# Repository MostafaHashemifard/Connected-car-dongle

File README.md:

# Connected-car-dongle
A device that is used to make cars connected to the cloud

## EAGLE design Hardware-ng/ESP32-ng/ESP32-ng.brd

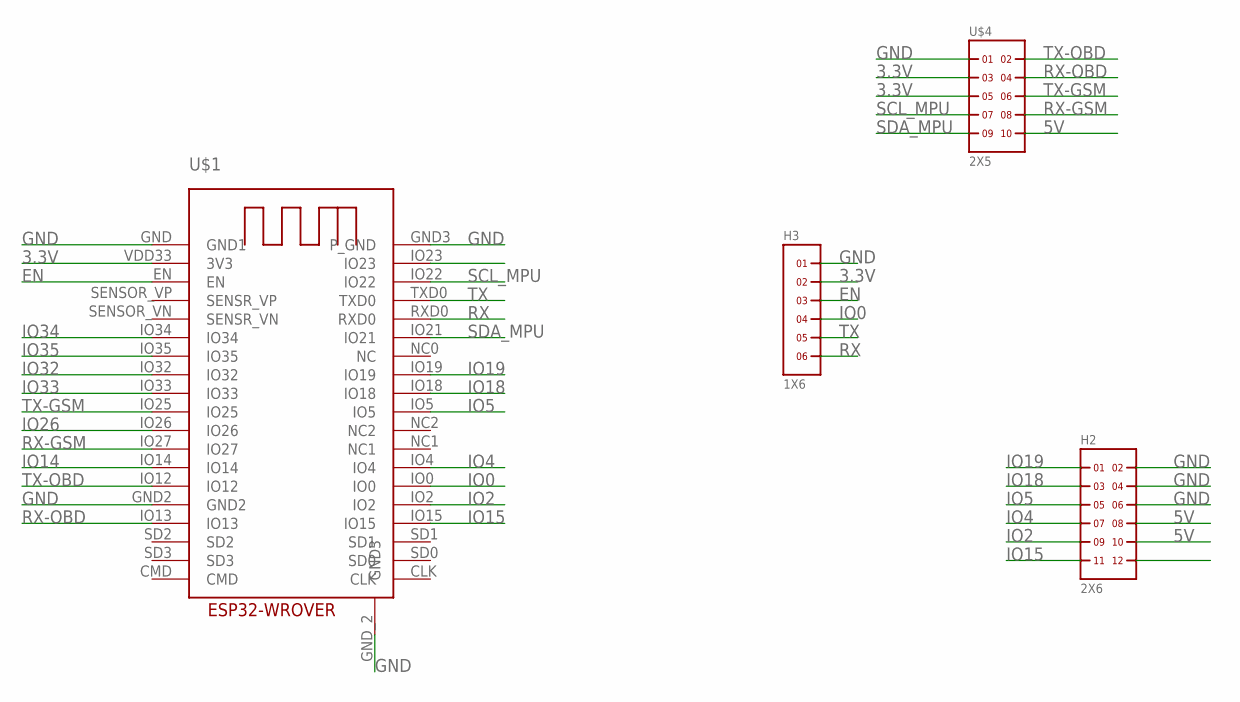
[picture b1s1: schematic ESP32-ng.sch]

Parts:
H2: 2X6
H3: 1X6
U$1: ESP32-WROVER
U$4: 2X5

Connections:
3.3V: H3.2, U$1.VDD33 (3V3), U$4.3, U$4.5
5V: H2.8, H2.10, U$4.10
EN: H3.3, U$1.EN
GND: H2.2, H2.4, H2.6, H3.1, U$1.GND (GND1), U$1.GND2, U$1.GND3 (P_GND), U$1.GND_2 (GND3), U$4.1
IO0: H3.4, U$1.IO0
IO2: H2.9, U$1.IO2
IO4: H2.7, U$1.IO4
IO5: H2.5, U$1.IO5
IO14: U$1.IO14
IO15: H2.11, U$1.IO15
IO18: H2.3, U$1.IO18
IO19: H2.1, U$1.IO19
IO26: U$1.IO26
IO32: U$1.IO32
IO33: U$1.IO33
IO34: U$1.IO34
IO35: U$1.IO35
RX: H3.6, U$1.RXD0
RX-GSM: U$1.IO27, U$4.8
RX-OBD: U$1.IO13, U$4.4
SCL_MPU: U$1.IO22, U$4.7
SDA_MPU: U$1.IO21, U$4.9
TX: H3.5, U$1.TXD0
TX-GSM: U$1.IO25, U$4.6
TX-OBD: U$1.IO12, U$4.2

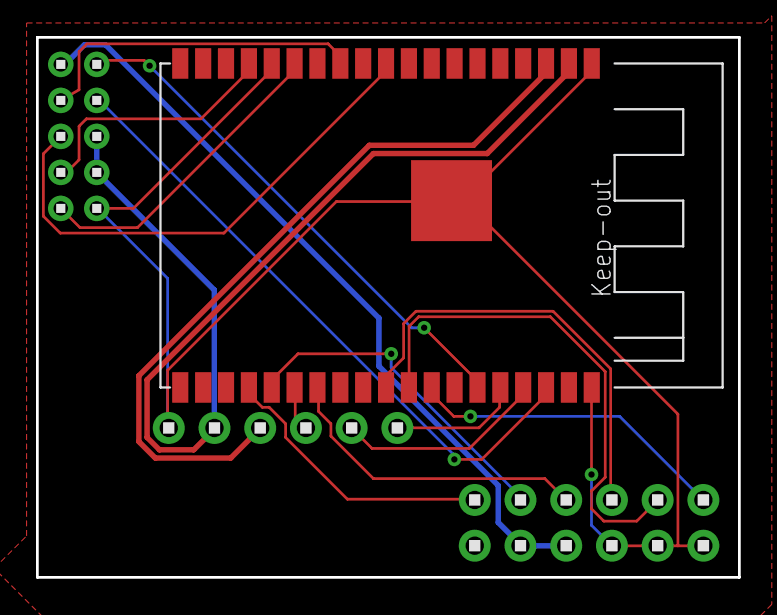
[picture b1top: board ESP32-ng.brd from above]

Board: 2 copper layers, 39.0 x 30.0 mm, 4 parts (0 on the bottom side), 19 nets.

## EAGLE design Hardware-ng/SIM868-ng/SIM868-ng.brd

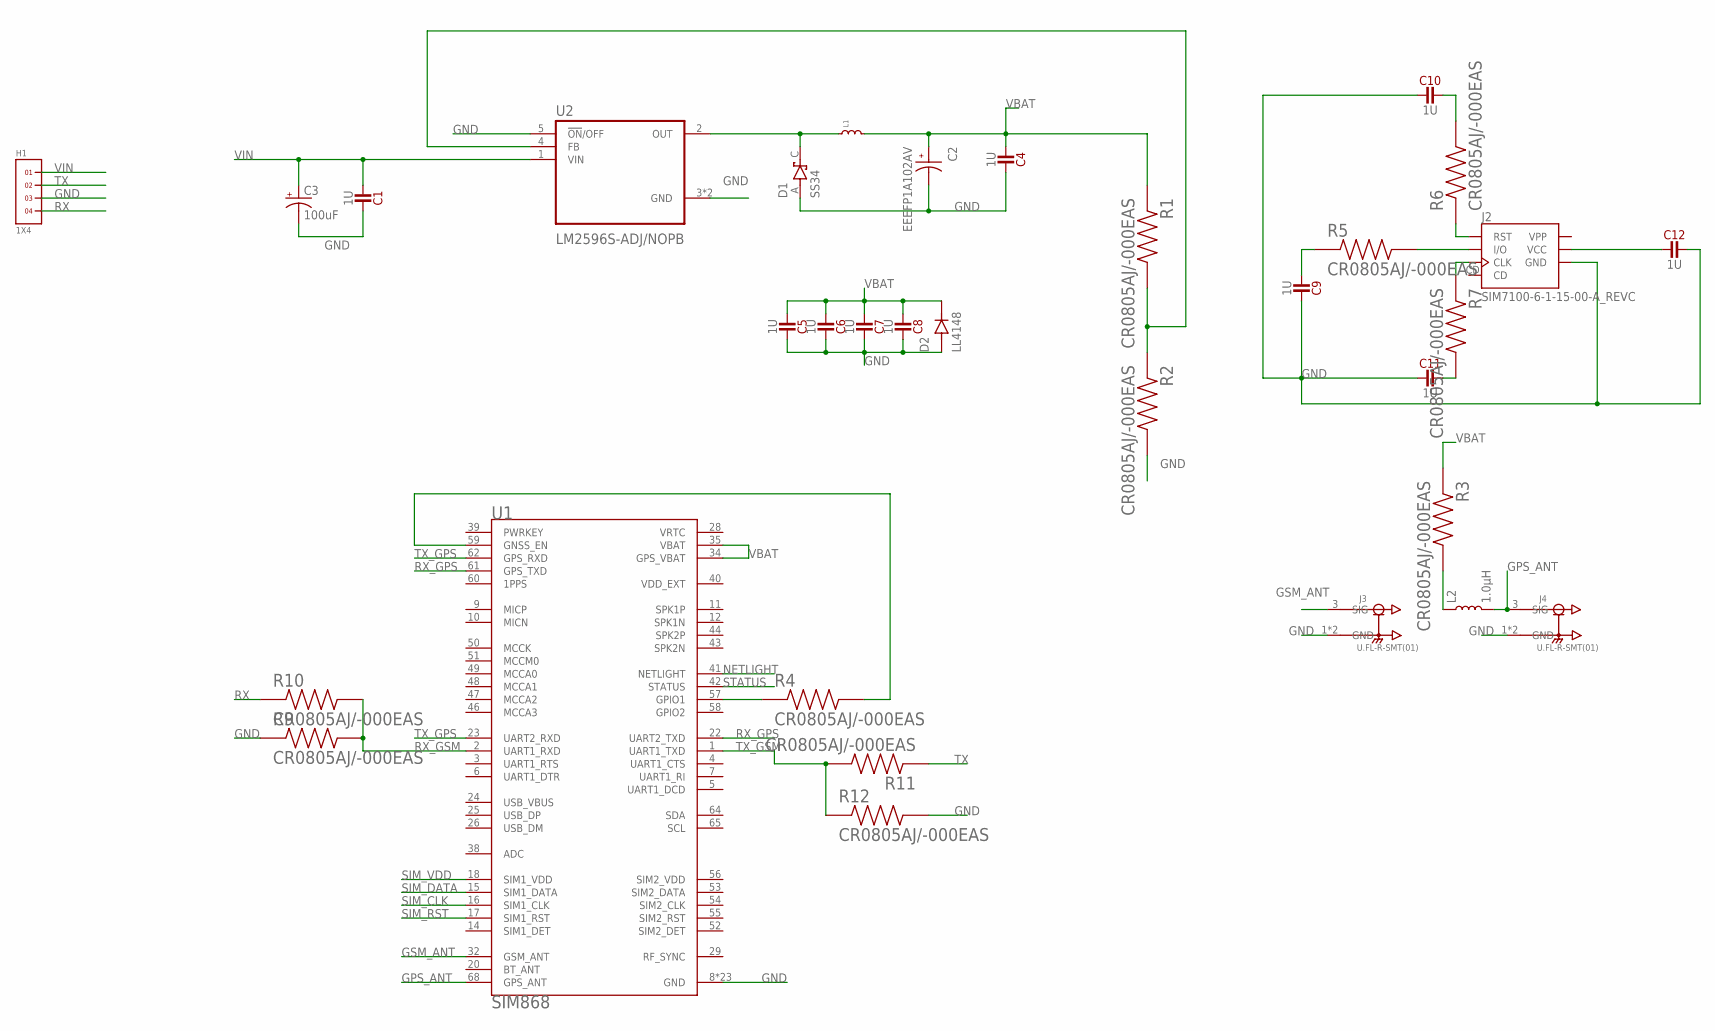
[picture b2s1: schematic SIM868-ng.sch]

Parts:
C1, C4, C5, C6, C7, C8, C9, C10, C11, C12: 1U; C-0805
C2: EEEFP1A102AV; CAP_EEEFP1A102AV
C3: 100uF; EIA3528
D1: SS34; DIOM7959X265N
D2: LL4148; DIO_LL4148
H1: 1X4
J2: SIM7100-6-1-15-00-A_REVC; GCT_SIM7100-6-1-15-00-A_REVC
J3, J4: U.FL-R-SMT(01); HRS_U.FL-R-SMT(01)
L1: INDUCTOR.XAL1010; XAL1010
L2: 1.0μH; 0805-WIDE
R1, R2, R3, R4, R5, R6, R7, R9, R10, R11, R12: CR0805AJ/-000EAS; RESC2012X60N
U1: SIM868; XCVR_SIM868
U2: LM2596S-ADJ/NOPB; VREG_LM2596S-ADJ/NOPB

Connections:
GND: C1.2, C2.2, C3.C (-), C4.2, C5.2, C6.2, C7.2, C8.2, C9.2, C10.1, C11.1, C12.2, D1.A, D2.A, H1.3, J2.C5 (GND), J3.1 (GND), J3.2 (GND), J4.1 (GND), J4.2 (GND), R2.2, R9.1, R12.2, U1.8 (GND), U1.13 (GND), U1.19 (GND), U1.21 (GND), U1.27 (GND), U1.30 (GND), U1.31 (GND), U1.33 (GND), U1.36 (GND), U1.37 (GND), U1.45 (GND), U1.63 (GND), U1.66 (GND), U1.67 (GND), U1.69 (GND), U1.70 (GND), U1.71 (GND), U1.72 (GND), U1.73 (GND), U1.74 (GND), U1.75 (GND), U1.76 (GND), U1.77 (GND), U2.3 (GND), U2.5 (!ON!/OFF), U2.6 (GND)
GPS_ANT: J4.3 (SIG), L2.2, U1.68 (GPS_ANT)
GSM_ANT: J3.3 (SIG), U1.32 (GSM_ANT)
unnamed: D1.C (K), L1.P$1 (1), U2.2 (OUT)
unnamed: R4.1, U1.57 (GPIO1)
unnamed: R1.2, R2.1, U2.4 (FB)
unnamed: L2.1, R3.2
unnamed: R4.2, U1.59 (GNSS_EN)
unnamed: J2.C7 (I/O), R5.2
unnamed: C9.1, R5.1
unnamed: J2.C2 (RST), R6.1
unnamed: C10.2, R6.2
unnamed: C11.2, R7.2
unnamed: J2.C3 (CLK), R7.1
unnamed: C12.1, J2.C1 (VCC)
NETLIGHT: U1.41 (NETLIGHT)
RX: H1.4, R10.1
RX_GPS: U1.22 (UART2_TXD), U1.61 (GPS_TXD)
RX_GSM: R9.2, R10.2, U1.2 (UART1_RXD)
SIM_CLK: U1.16 (SIM1_CLK)
SIM_DATA: U1.15 (SIM1_DATA)
SIM_RST: U1.17 (SIM1_RST)
SIM_VDD: U1.18 (SIM1_VDD)
STATUS: U1.42 (STATUS)
TX: H1.2, R11.1
TX_GPS: U1.23 (UART2_RXD), U1.62 (GPS_RXD)
TX_GSM: R11.2, R12.1, U1.1 (UART1_TXD)
VBAT: C2.1, C4.1, C5.1, C6.1, C7.1, C8.1, D2.C, L1.P$2 (2), R1.1, R3.1, U1.34 (GPS_VBAT), U1.35 (VBAT)
VIN: C1.1, C3.A (+), H1.1, U2.1 (VIN)
VPP: J2.C6 (VPP)
VRTC: U1.28 (VRTC)

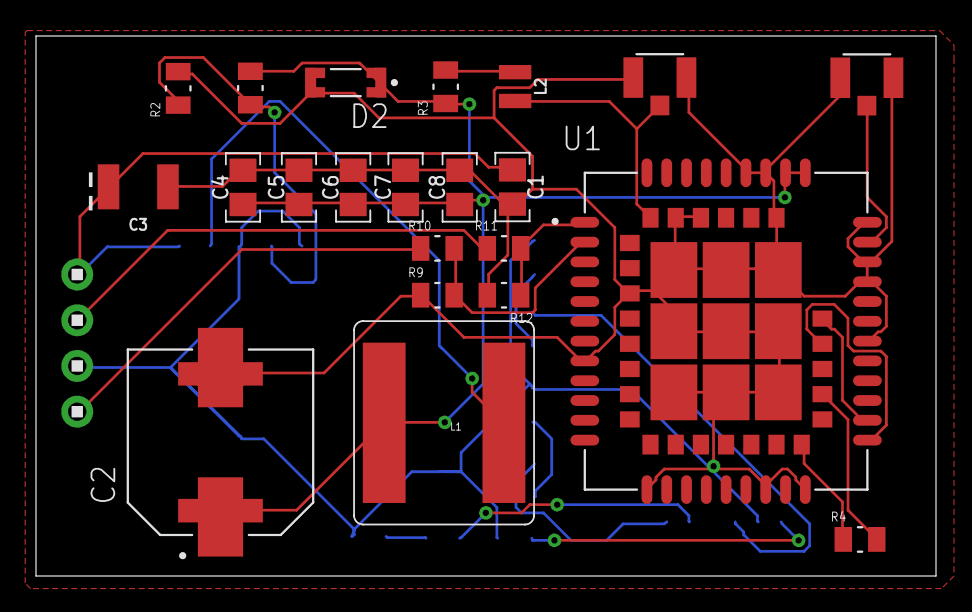
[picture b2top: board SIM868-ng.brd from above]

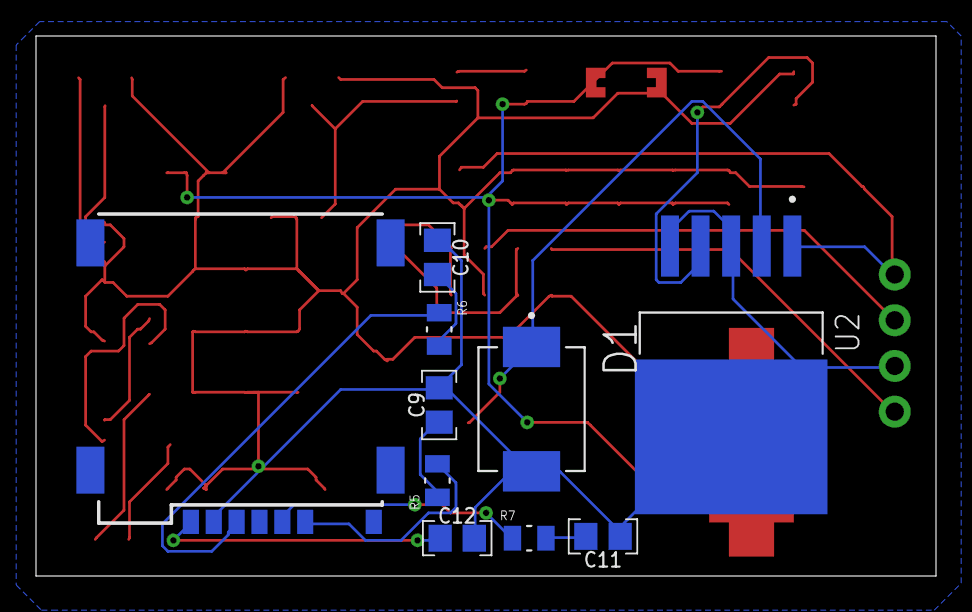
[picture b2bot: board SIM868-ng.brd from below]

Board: 2 copper layers, 50.0 x 30.0 mm, 33 parts (10 on the bottom side), 23 nets.

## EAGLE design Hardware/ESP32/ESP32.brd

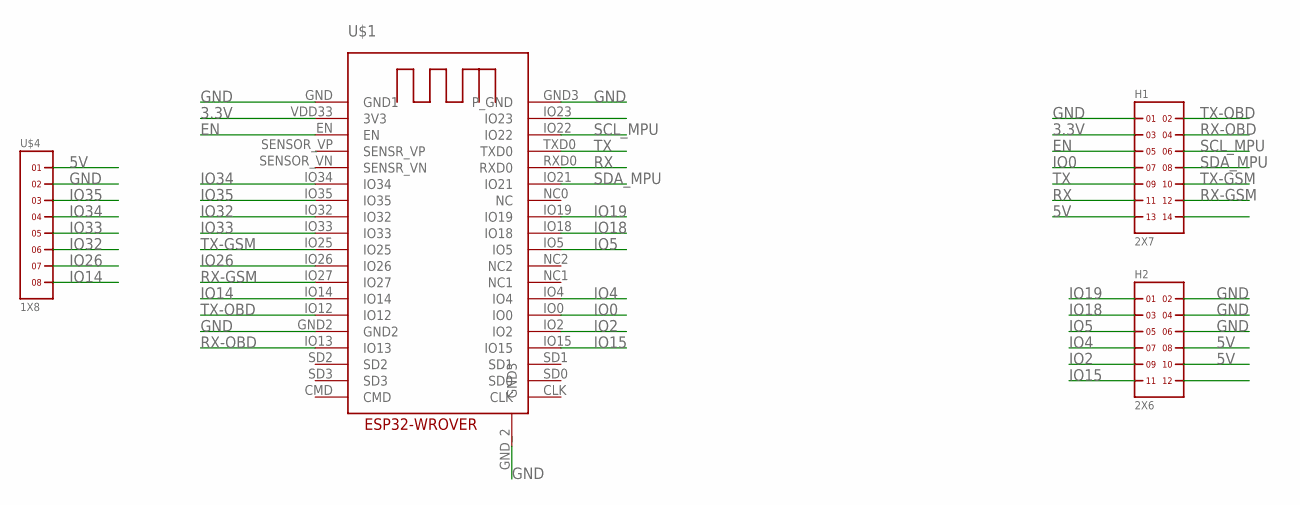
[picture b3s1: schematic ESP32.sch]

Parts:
H1: 2X7
H2: 2X6
U$1: ESP32-WROVER
U$4: 1X8

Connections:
3.3V: H1.3, U$1.VDD33 (3V3)
5V: H1.13, H2.8, H2.10, U$4.1
EN: H1.5, U$1.EN
GND: H1.1, H2.2, H2.4, H2.6, U$1.GND (GND1), U$1.GND2, U$1.GND3 (P_GND), U$1.GND_2 (GND3), U$4.2
IO0: H1.7, U$1.IO0
IO2: H2.9, U$1.IO2
IO4: H2.7, U$1.IO4
IO5: H2.5, U$1.IO5
IO14: U$1.IO14, U$4.8
IO15: H2.11, U$1.IO15
IO18: H2.3, U$1.IO18
IO19: H2.1, U$1.IO19
IO26: U$1.IO26, U$4.7
IO32: U$1.IO32, U$4.6
IO33: U$1.IO33, U$4.5
IO34: U$1.IO34, U$4.4
IO35: U$1.IO35, U$4.3
RX: H1.11, U$1.RXD0
RX-GSM: H1.12, U$1.IO27
RX-OBD: H1.4, U$1.IO13
SCL_MPU: H1.6, U$1.IO22
SDA_MPU: H1.8, U$1.IO21
TX: H1.9, U$1.TXD0
TX-GSM: H1.10, U$1.IO25
TX-OBD: H1.2, U$1.IO12

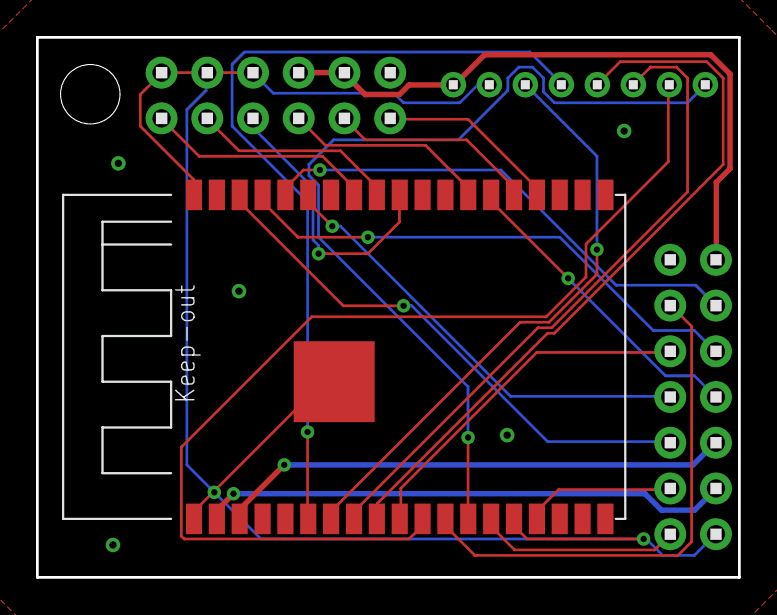
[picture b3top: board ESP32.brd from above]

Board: 2 copper layers, 39.0 x 30.0 mm, 5 parts (0 on the bottom side), 25 nets.

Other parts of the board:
JP4: STAND-OFF

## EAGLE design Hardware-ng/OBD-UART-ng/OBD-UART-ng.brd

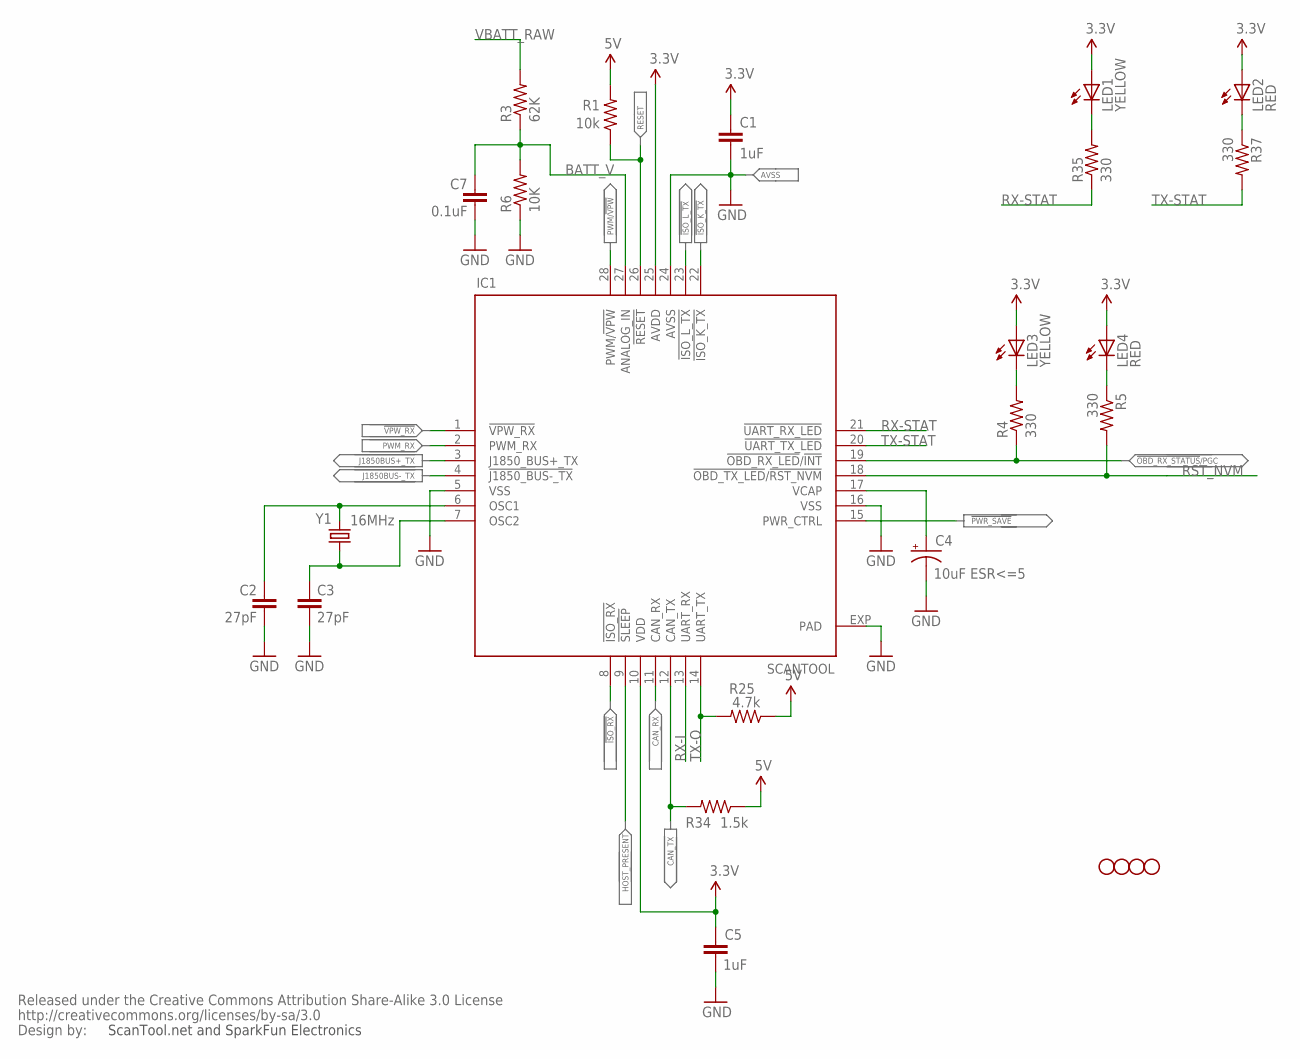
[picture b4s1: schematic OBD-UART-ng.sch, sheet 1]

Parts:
C1, C5: 1uF; 0402-CAP
C2, C3: 27pF; 0402-CAP
C4: 10uF ESR<=5; EIA3216
C7: 0.1uF; 0402-CAP
IC1: SCANTOOL; _STN_SCANTOOL_QFN-28-S
JP4, JP5, JP6, JP7: STAND-OFF
LED1, LED3: YELLOW; LED-0603
LED2, LED4: RED; LED-0603
R1: 10k; 0402-RES
R3: 62K; 0402-RES
R4, R5, R35, R37: 330; 0402-RES
R6: 10K; 0402-RES
R25: 4.7k; 0402-RES
R34: 1.5k; 0402-RES
U$1: CREATIVE_COMMONS
Y1: 16MHz; CRYSTAL-SMD-5X3

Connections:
3.3V: C1.1, C5.1, IC1.10 (VDD), IC1.25 (AVDD), LED1.A, LED2.A, LED3.A, LED4.A; also elsewhere on the board
5V: R1.2, R25.1, R34.1; also elsewhere on the board
!ISO_K_TX: IC1.22 (!ISO_K_TX); also elsewhere on the board
!ISO_L_TX: IC1.23 (!ISO_L_TX); also elsewhere on the board
!ISO_RX: IC1.8 (!ISO_RX); also elsewhere on the board
!OBD_RX_STATUS!/PGC: IC1.19 (!OBD_RX_LED!/!INT), R4.1
!PWR_SAVE: IC1.15 (PWR_CTRL)
!VPW_RX: IC1.1 (!VPW_RX); also elsewhere on the board
BATT_V: C7.1, IC1.27 (ANALOG_IN), R3.1, R6.2
CAN_RX: IC1.11 (CAN_RX); also elsewhere on the board
CAN_TX: IC1.12 (CAN_TX), R34.2; also elsewhere on the board
GND: C1.2, C2.2, C3.2, C4.C (-), C5.2, C7.2, IC1.5 (VSS), IC1.16 (VSS), IC1.24 (AVSS), IC1.EXP (PAD), R6.1; also elsewhere on the board
HOST_PRESENT: IC1.9 (!SLEEP)
J1850BUS+_TX: IC1.3 (J1850_BUS+_TX); also elsewhere on the board
J1850BUS-_TX: IC1.4 (!J1850_BUS-_TX); also elsewhere on the board
unnamed: C4.A (+), IC1.17 (VCAP)
unnamed: LED3.C, R4.2
unnamed: LED4.C, R5.1
unnamed: LED1.C, R35.2
unnamed: LED2.C, R37.1
OSC1: C2.1, IC1.6 (OSC1), Y1.3 (2)
OSC2: C3.1, IC1.7 (OSC2), Y1.1
PWM/!VPW: IC1.28 (PWM/!VPW); also elsewhere on the board
PWM_RX: IC1.2 (PWM_RX); also elsewhere on the board
RESET: IC1.26 (!RESET), R1.1
RST_NVM: IC1.18 (!OBD_TX_LED!/!RST_NVM), R5.2
RX-I: IC1.13 (UART_RX); also elsewhere on the board
RX-STAT: IC1.21 (!UART_RX_LED), R35.1
TX-O: IC1.14 (UART_TX), R25.2; also elsewhere on the board
TX-STAT: IC1.20 (!UART_TX_LED), R37.2
VBATT_RAW: R3.2; also elsewhere on the board

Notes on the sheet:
AVSS
ScanTool.net and SparkFun Electronics

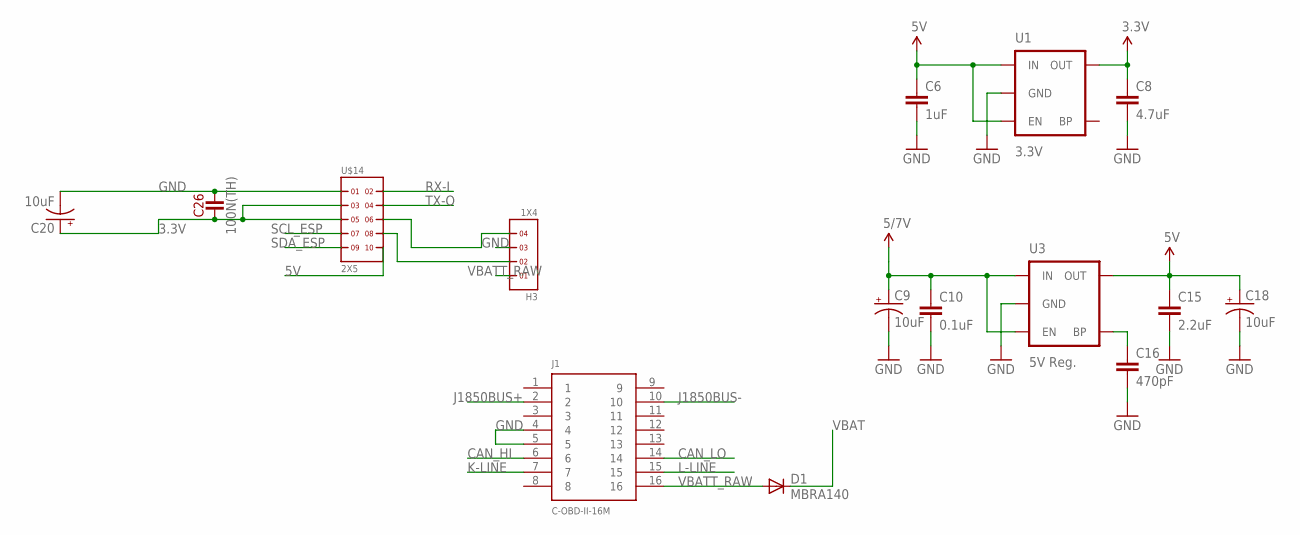
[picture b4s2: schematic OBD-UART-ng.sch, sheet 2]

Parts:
C6: 1uF; 0402-CAP
C8: 4.7uF; 0402-CAP
C9, C18, C20: 10uF; EIA3216
C10: 0.1uF; 0402-CAP
C15: 2.2uF; 0402-CAP
C16: 470pF; 0402-CAP
C26: 100N(TH); C050-024X044
D1: MBRA140; SMA-DIODE
H3: 1X4
J1: C-OBD-II-16M; COMTECH_C-OBD-II-16M
U1: 3.3V; SOT23-5
U3: 5V Reg.; SOT23-5
U$14: 2X5

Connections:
3.3V: C8.1, C20.A (+), C26.1, U1.5 (OUT), U$14.3, U$14.5; also elsewhere on the board
5V: C6.1, C15.1, C18.A (+), U1.1 (IN), U1.3 (EN), U3.5 (OUT), U$14.10; also elsewhere on the board
CAN_HI: J1.6; also elsewhere on the board
CAN_LO: J1.14; also elsewhere on the board
GND: C6.2, C8.2, C9.C (-), C10.2, C15.2, C16.2, C18.C (-), C20.C (-), C26.2, H3.3, J1.4, J1.5, U1.2 (GND), U3.2 (GND), U$14.1; also elsewhere on the board
J1850BUS+: J1.2; also elsewhere on the board
J1850BUS-: J1.10; also elsewhere on the board
K-LINE: J1.7; also elsewhere on the board
L-LINE: J1.15; also elsewhere on the board
unnamed: H3.4, U$14.6
unnamed: H3.2, U$14.8
unnamed: C16.1, U3.4 (BP)
RX-I: U$14.2; also elsewhere on the board
SCL_ESP: U$14.7; also elsewhere on the board
SDA_ESP: U$14.9; also elsewhere on the board
TX-O: U$14.4; also elsewhere on the board
VBAT: D1.C; also elsewhere on the board
VBATT_RAW: D1.A, H3.1, J1.16; also elsewhere on the board
VCC: C9.A (+), C10.1, U3.1 (IN), U3.3 (EN); also elsewhere on the board

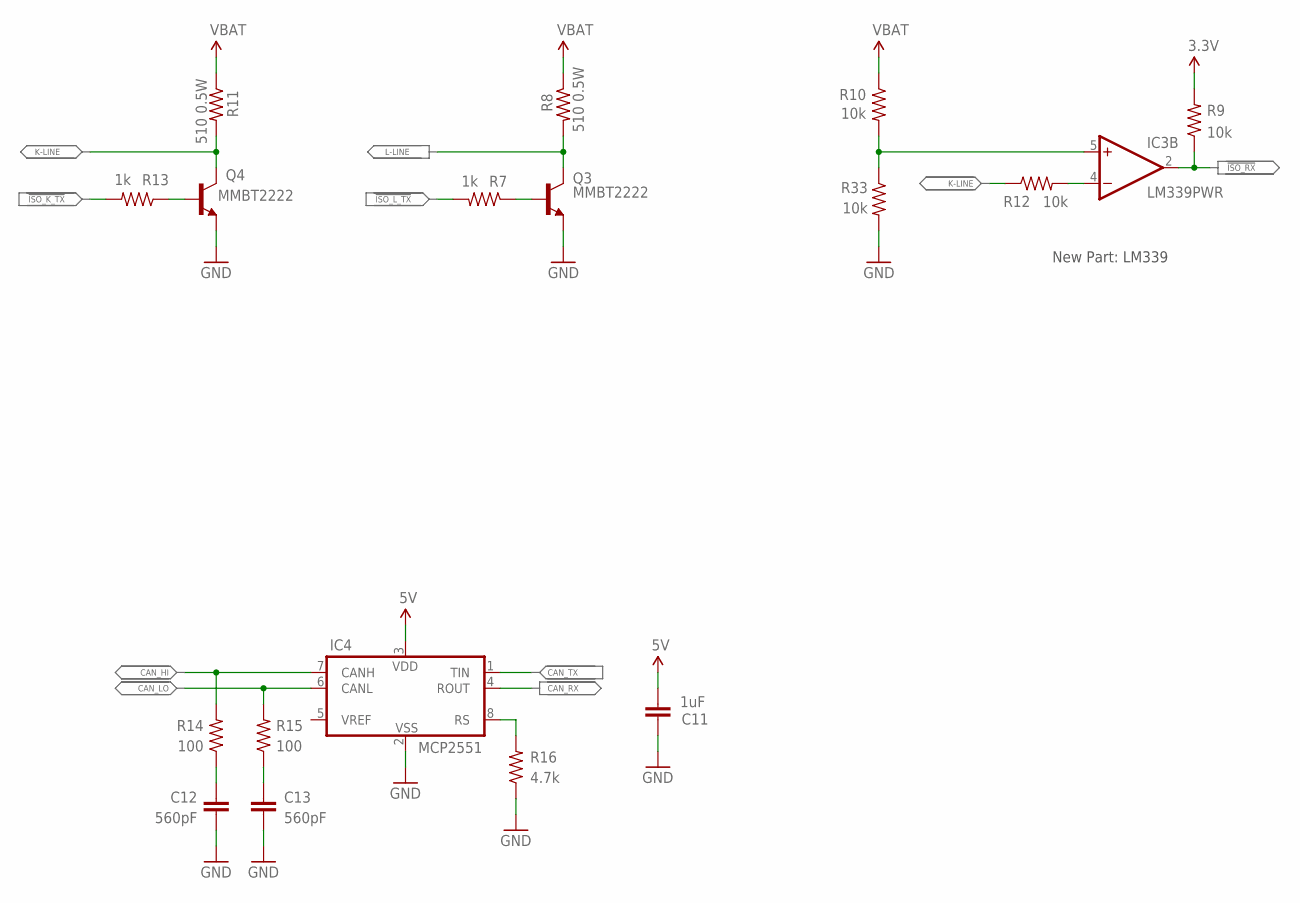
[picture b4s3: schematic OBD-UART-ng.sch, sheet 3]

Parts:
C11: 1uF; 0402-CAP
C12, C13: 560pF; 0402-CAP
IC3: LM339PWR; TSSOP-14
IC4: MCP2551; SO-8
Q3, Q4: MMBT2222; SOT23-3
R7, R13: 1k; 0402-RES
R8, R11: 510 0.5W; 2010
R9, R10, R12, R33: 10k; 0402-RES
R14, R15: 100; 0402-RES
R16: 4.7k; 0402-RES

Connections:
3.3V: R9.2; also elsewhere on the board
5V: C11.1, IC4.3 (VDD); also elsewhere on the board
!ISO_K_TX: R13.2; also elsewhere on the board
!ISO_L_TX: R7.2; also elsewhere on the board
!ISO_RX: IC3.2 (OUT), R9.1; also elsewhere on the board
CAN_HI: IC4.7 (CANH), R14.2; also elsewhere on the board
CAN_LO: IC4.6 (CANL), R15.2; also elsewhere on the board
CAN_RX: IC4.4 (ROUT); also elsewhere on the board
CAN_TX: IC4.1 (TIN); also elsewhere on the board
GND: C11.2, C12.2, C13.2, IC4.2 (VSS), Q3.2 (E), Q4.2 (E), R16.1, R33.2; also elsewhere on the board
K-LINE: Q4.3 (C), R11.2, R12.1; also elsewhere on the board
L-LINE: Q3.3 (C), R8.2; also elsewhere on the board
unnamed: Q4.1 (B), R13.1
unnamed: Q3.1 (B), R7.1
unnamed: IC3.5 (+IN), R10.2, R33.1
unnamed: C12.1, R14.1
unnamed: IC4.8 (RS), R16.2
unnamed: IC3.4 (-IN), R12.2
unnamed: C13.1, R15.1
VBAT: R8.1, R10.1, R11.1; also elsewhere on the board

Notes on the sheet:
New Part: LM339

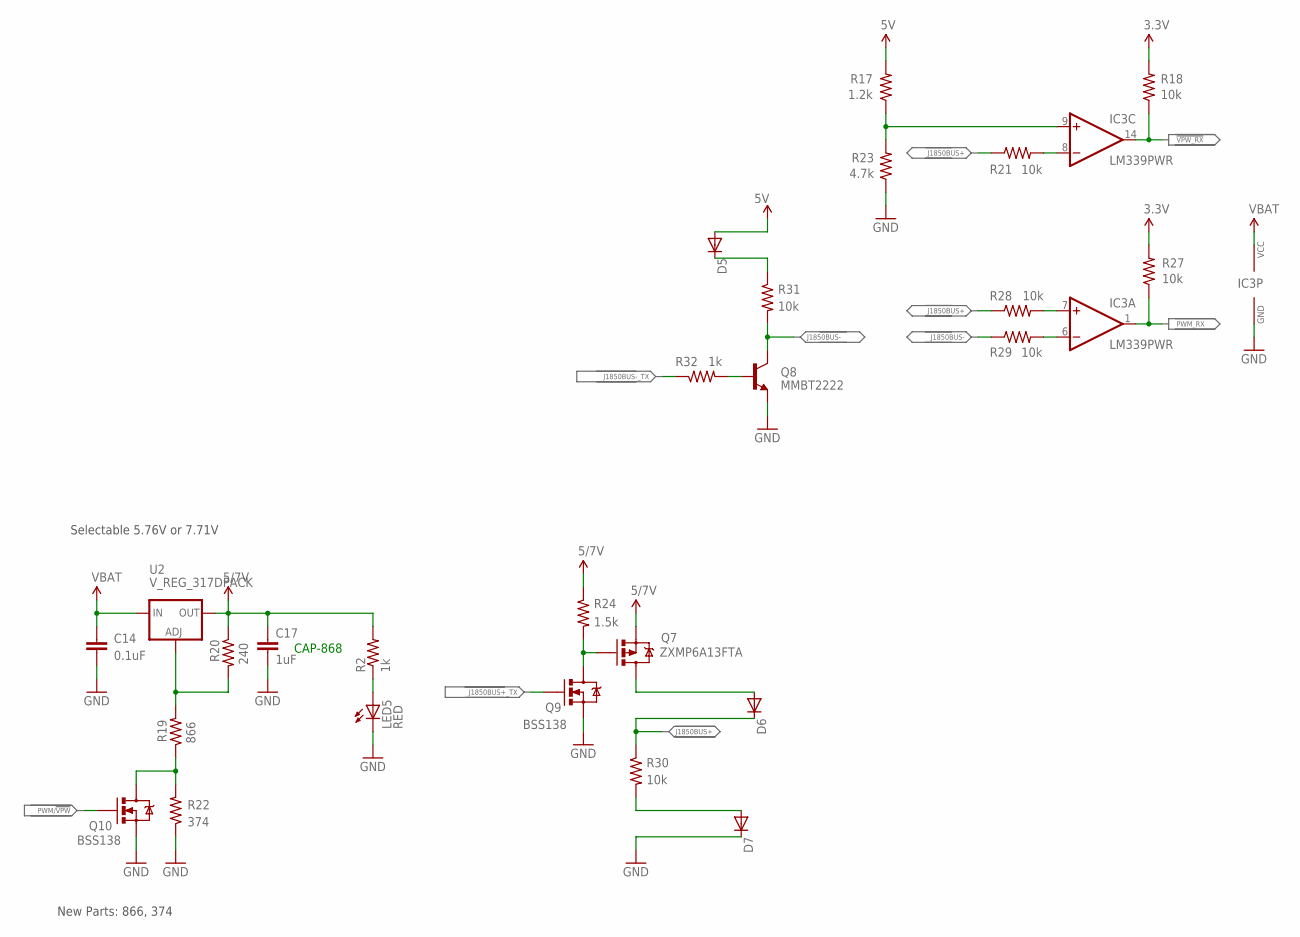
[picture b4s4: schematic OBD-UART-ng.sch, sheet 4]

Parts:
C14: 0.1uF; 0402-CAP
C17: 1uF; 0402-CAP
D5, D6, D7: DIODESOT23; SOT23-3
IC3: LM339PWR; TSSOP-14
LED5: RED; LED-0603
Q7: ZXMP6A13FTA; SOT23
Q8: MMBT2222; SOT23-3
Q9, Q10: BSS138; SOT23-3
R2, R32: 1k; 0402-RES
R17: 1.2k; 0402-RES
R18, R21, R27, R28, R29, R30, R31: 10k; 0402-RES
R19: 866; 0402-RES
R20: 240; 0402-RES
R22: 374; 0402-RES
R23: 4.7k; 0402-RES
R24: 1.5k; 0402-RES
U2: V_REG_317DPACK; V-REG_DPACK

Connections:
3.3V: R18.2, R27.2; also elsewhere on the board
5V: D5.1 (A), R17.2; also elsewhere on the board
!VPW_RX: IC3.14 (OUT), R18.1; also elsewhere on the board
GND: C14.2, C17.2, D7.3 (C), IC3.12 (GND), LED5.C, Q8.2 (E), Q9.2 (S), Q10.2 (S), R22.1, R23.1; also elsewhere on the board
J1850BUS+: D6.3 (C), R21.1, R28.1, R30.1; also elsewhere on the board
J1850BUS+_TX: Q9.1 (G); also elsewhere on the board
J1850BUS-: Q8.3 (C), R29.1, R31.2; also elsewhere on the board
J1850BUS-_TX: R32.1; also elsewhere on the board
unnamed: IC3.7 (+IN), R28.2
unnamed: IC3.6 (-IN), R29.2
unnamed: IC3.8 (-IN), R21.2
unnamed: R19.2, R20.2, U2.1 (ADJ)
unnamed: D6.1 (A), Q7.3 (D)
unnamed: IC3.9 (+IN), R17.1, R23.2
unnamed: D5.3 (C), R31.1
unnamed: Q7.1 (G), Q9.3 (D), R24.2
unnamed: Q10.3 (D), R19.1, R22.2
unnamed: D7.1 (A), R30.2
unnamed: Q8.1 (B), R32.2
unnamed: LED5.A, R2.1
PWM/!VPW: Q10.1 (G); also elsewhere on the board
PWM_RX: IC3.1 (OUT), R27.1; also elsewhere on the board
VBAT: C14.1, IC3.3 (VCC), U2.3 (IN); also elsewhere on the board
VCC: C17.1, Q7.2 (S), R2.2, R20.1, R24.1, U2.4 (OUT); also elsewhere on the board

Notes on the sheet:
Selectable 5.76V or 7.71V
New Parts: 866, 374
CAP-868

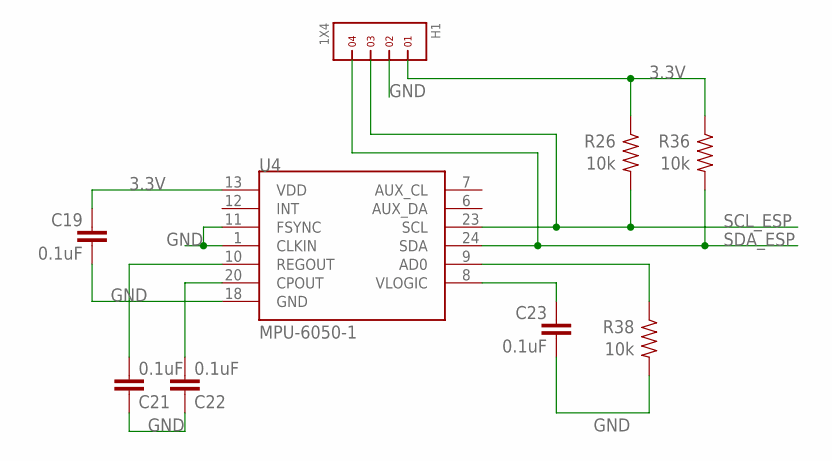
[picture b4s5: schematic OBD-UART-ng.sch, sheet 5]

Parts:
C19, C21, C22, C23: 0.1uF; 0402-CAP
H1: 1X4
R26, R36, R38: 10k; 0402-RES
U4: MPU-6050-1; QFN-24-4MM2

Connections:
3.3V: C19.1, H1.1, R26.1, R36.1, U4.13 (VDD); also elsewhere on the board
GND: C19.2, C21.1, C22.1, C23.2, H1.2, R38.2, U4.1 (CLKIN), U4.11 (FSYNC), U4.18 (GND); also elsewhere on the board
unnamed: C21.2, U4.10 (REGOUT)
unnamed: C22.2, U4.20 (CPOUT)
unnamed: R38.1, U4.9 (AD0)
unnamed: C23.1, U4.8 (VLOGIC)
SCL_ESP: H1.3, R26.2, U4.23 (SCL); also elsewhere on the board
SDA_ESP: H1.4, R36.2, U4.24 (SDA); also elsewhere on the board

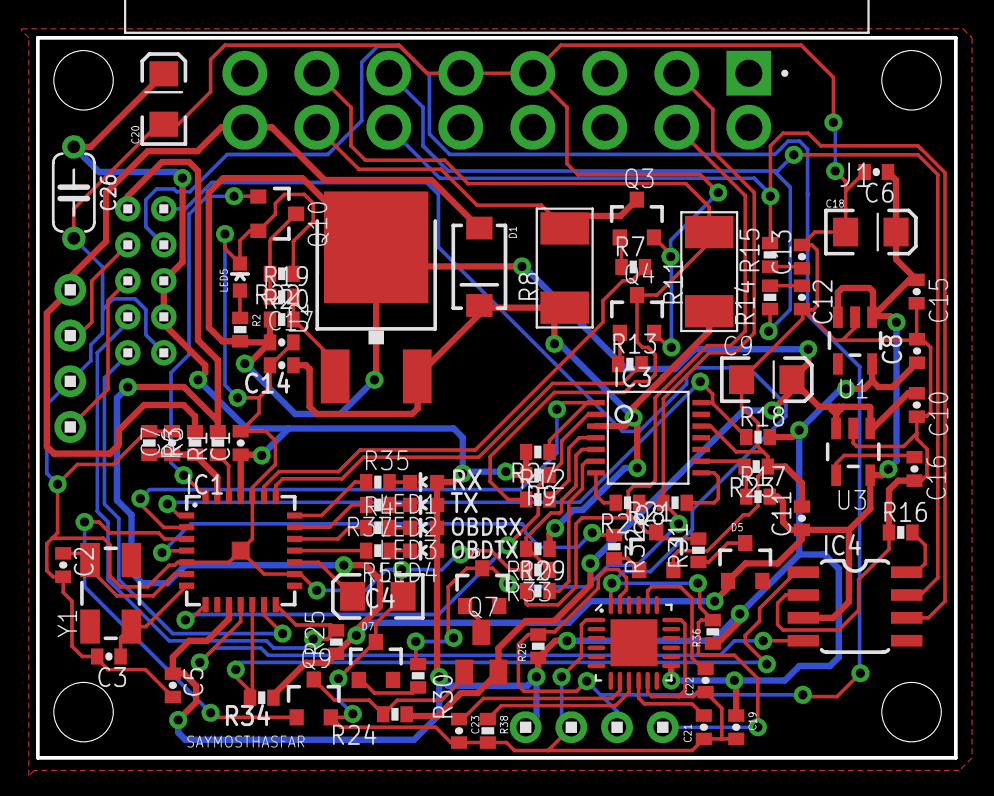
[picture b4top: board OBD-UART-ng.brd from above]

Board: 2 copper layers, 51.0 x 40.0 mm, 94 parts (0 on the bottom side), 65 nets.

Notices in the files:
parts and their libraries:
SparkFun: Released under the Creative Commons Attribution Share-Alike 3.0 License
SparkFun: http://creativecommons.org/licenses/by-sa/3.0
SparkFun-Capacitors: Licensing: Creative Commons ShareAlike 4.0 International - https://creativecommons.org/licenses/by-sa/4.0
